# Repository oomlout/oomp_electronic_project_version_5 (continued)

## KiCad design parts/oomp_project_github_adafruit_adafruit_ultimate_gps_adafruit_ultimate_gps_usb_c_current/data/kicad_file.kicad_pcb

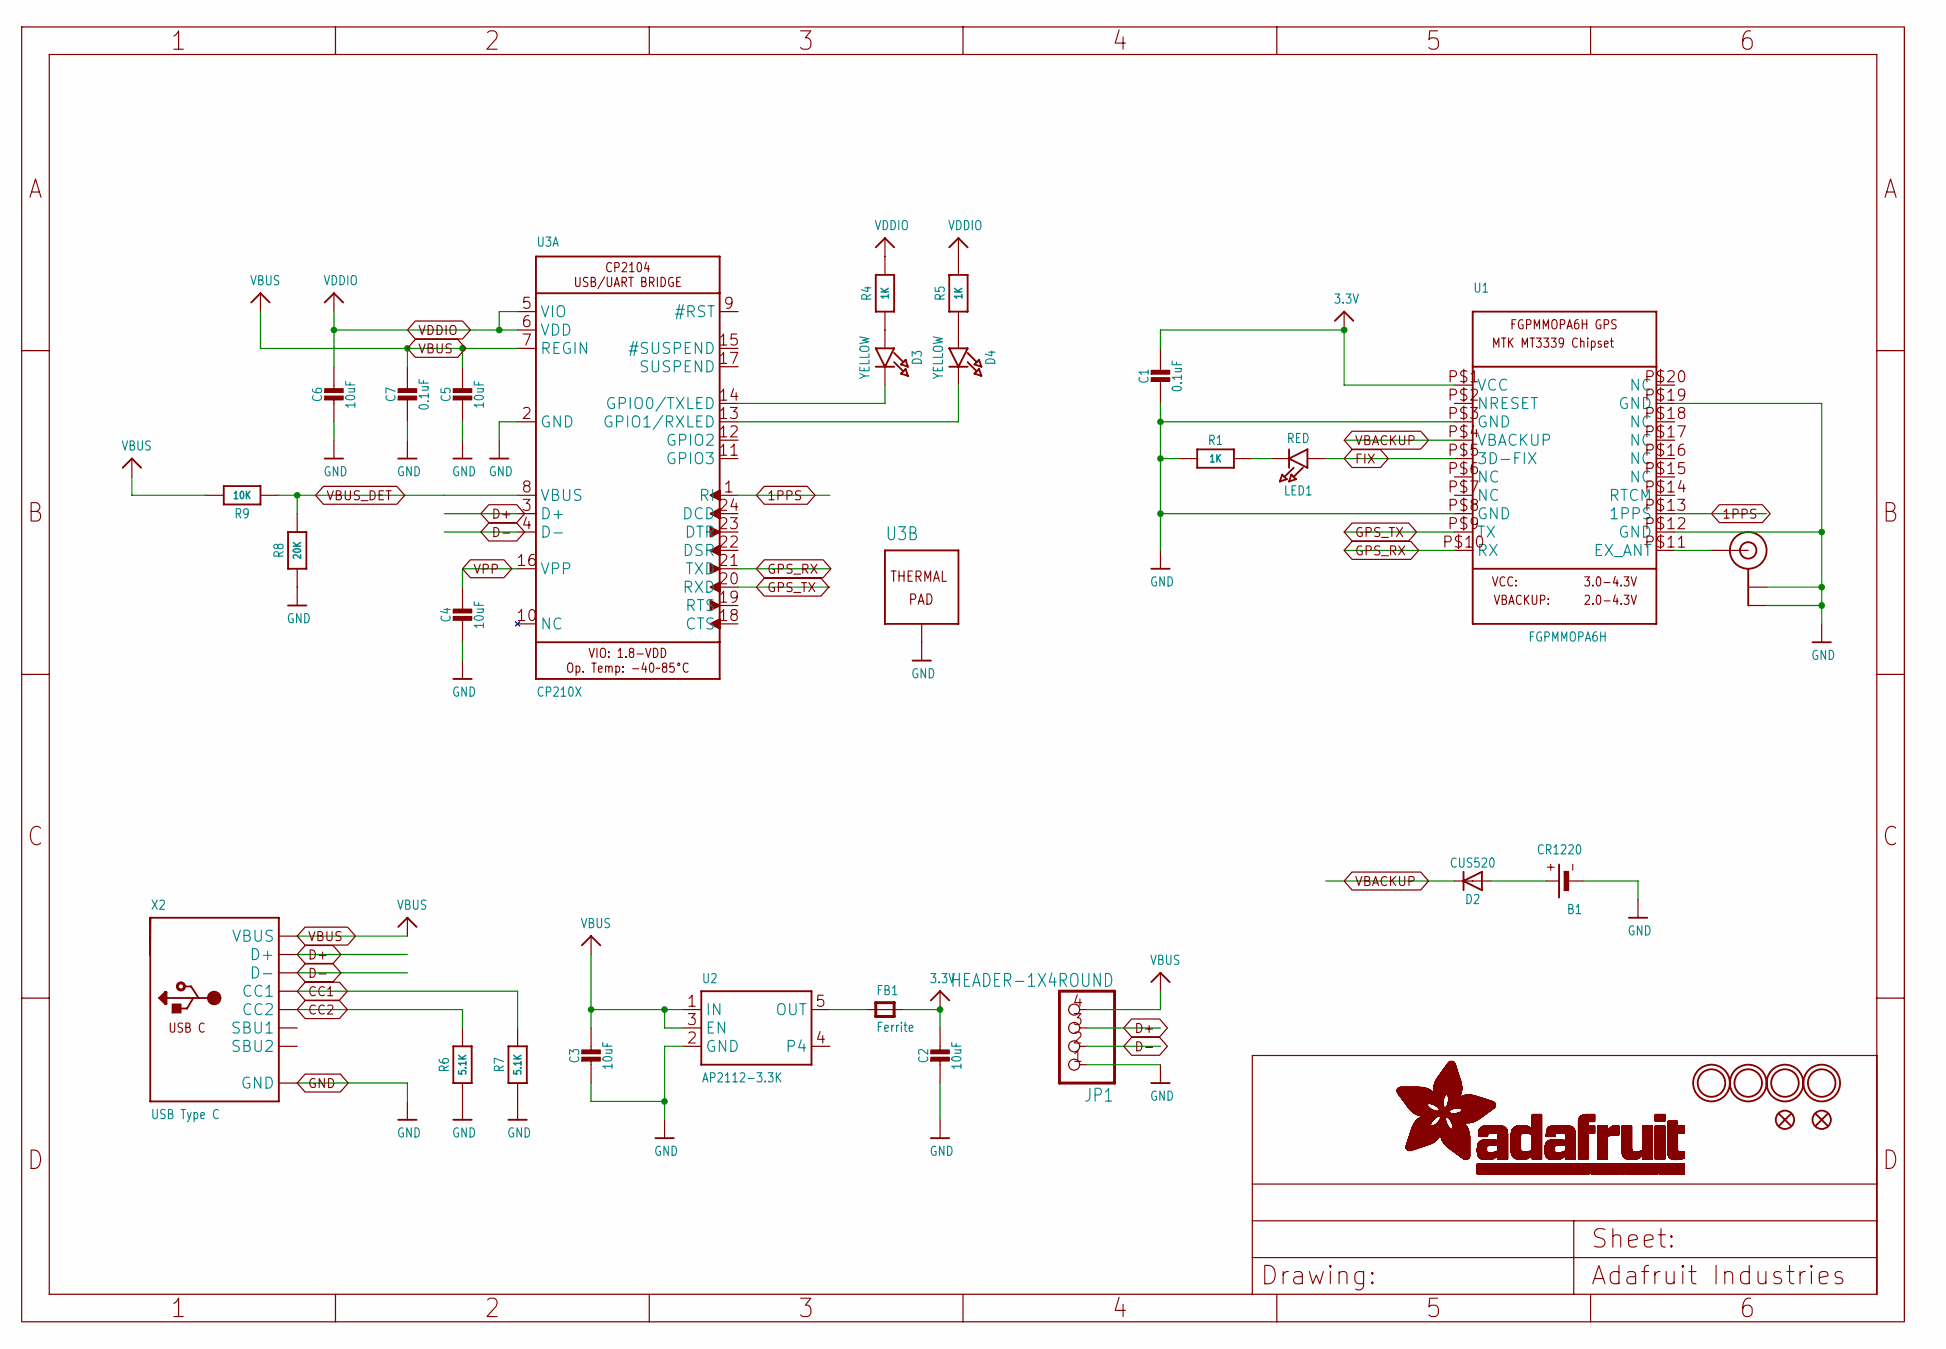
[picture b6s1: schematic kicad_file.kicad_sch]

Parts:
B1: CR1220
C1, C7: 0.1uF; 0603-NO
C2, C3, C4, C5, C6: 10uF; 0805-NO
D2: CUS520; SOD-323
D3, D4: YELLOW; CHIPLED_0805_NOOUTLINE
FB1: Ferrite; 0805-NO
FID1, FID2: FIDUCIAL_1MM
JP1: HEADER-1X4ROUND; 1X04_ROUND
LED1: RED; CHIPLED_0805_NOOUTLINE
R1, R4, R5: 1K; 0603-NO
R6, R7: 5.1K; 0603-NO
R8: 20K; 0603-NO
R9: 10K; 0603-NO
U1: FGPMMOPA6H
U2: AP2112-3.3K; SOT23-5
U3: CP210X; QFN24_4MM_SMSC
U$8, U$9, U$35, U$36: MOUNTINGHOLE2.5; MOUNTINGHOLE_2.5_PLATED
U$20: U.FL
X2: USB Type C; USB_C_CUSB31-CFM2AX-01-X

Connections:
1PPS: U1.P$13 (1PPS), U3.1 (RI)
3.3V: C1.1, C2.1, FB1.2, U1.P$1 (VCC)
CC1: R7.2, X2.A5 (CC1)
CC2: R6.2, X2.B5 (CC2)
D+: JP1.3, U3.3 (D+), X2.A6 (D+), X2.B6 (D+)
D-: JP1.2, U3.4 (D-), X2.A7 (D-), X2.B7 (D-)
FIX: LED1.A, U1.P$5 (3D-FIX)
GND: B1.-, C1.2, C2.2, C3.2, C4.2, C5.2, C6.2, C7.2, JP1.1, R1.1, R6.1, R7.1, R8.1, U1.P$3 (GND), U1.P$8 (GND), U1.P$12 (GND), U1.P$19 (GND), U2.2 (GND), U3.2 (GND), U3.THERM (TP), U$20.P$1 (GND), U$20.P$2 (GND), X2.A1B12 (GND), X2.B1A12 (GND)
GPS_RX: U1.P$10 (RX), U3.21 (TXD)
GPS_TX: U1.P$9 (TX), U3.20 (RXD)
unnamed: B1.+$1 (+), B1.+$2 (+), D2.A
unnamed: LED1.C, R1.2
unnamed: FB1.1, U2.5 (OUT)
unnamed: U1.P$11 (EX_ANT), U$20.P$3 (SIGNAL)
unnamed: D3.A, R4.1
unnamed: D4.A, R5.1
unnamed: D3.C, U3.14 (GPIO0/TXLED)
unnamed: D4.C, U3.13 (GPIO1/RXLED)
VBACKUP: D2.C, U1.P$4 (VBACKUP)
VBUS: C3.1, C5.1, C7.1, JP1.4, R9.2, U2.1 (IN), U2.3 (EN), U3.7 (REGIN), X2.A4B9 (VBUS), X2.B4A9 (VBUS)
VBUS_DET: R8.2, R9.1, U3.8 (VBUS)
VDDIO: C6.1, R4.2, R5.2, U3.5 (VIO), U3.6 (VDD)
VPP: C4.1, U3.16 (VPP)

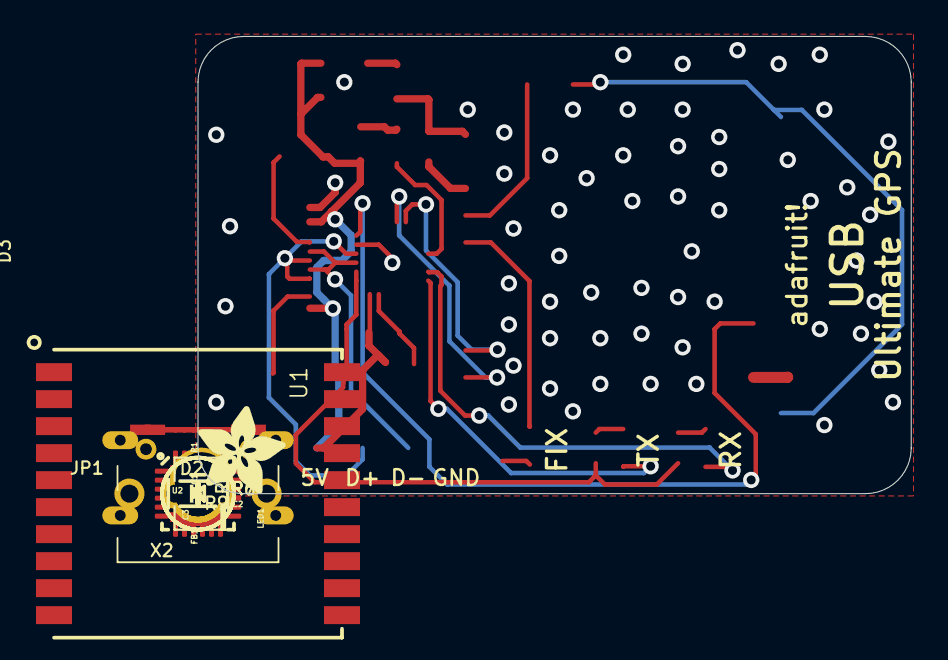
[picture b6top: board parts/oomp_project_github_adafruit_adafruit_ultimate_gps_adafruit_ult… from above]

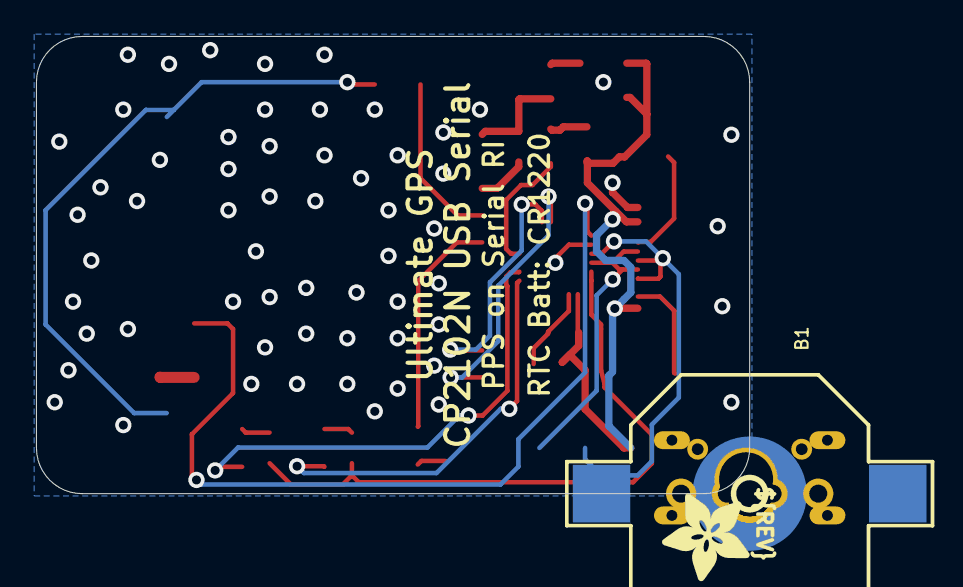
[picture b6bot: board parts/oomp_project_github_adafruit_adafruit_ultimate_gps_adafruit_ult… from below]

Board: 2 copper layers, 39.6 x 25.4 mm, 35 parts (3 on the bottom side), 23 nets.

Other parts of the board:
U$13, U$18: ADAFRUIT_5MM
U$16: PCBFEAT-REV-040

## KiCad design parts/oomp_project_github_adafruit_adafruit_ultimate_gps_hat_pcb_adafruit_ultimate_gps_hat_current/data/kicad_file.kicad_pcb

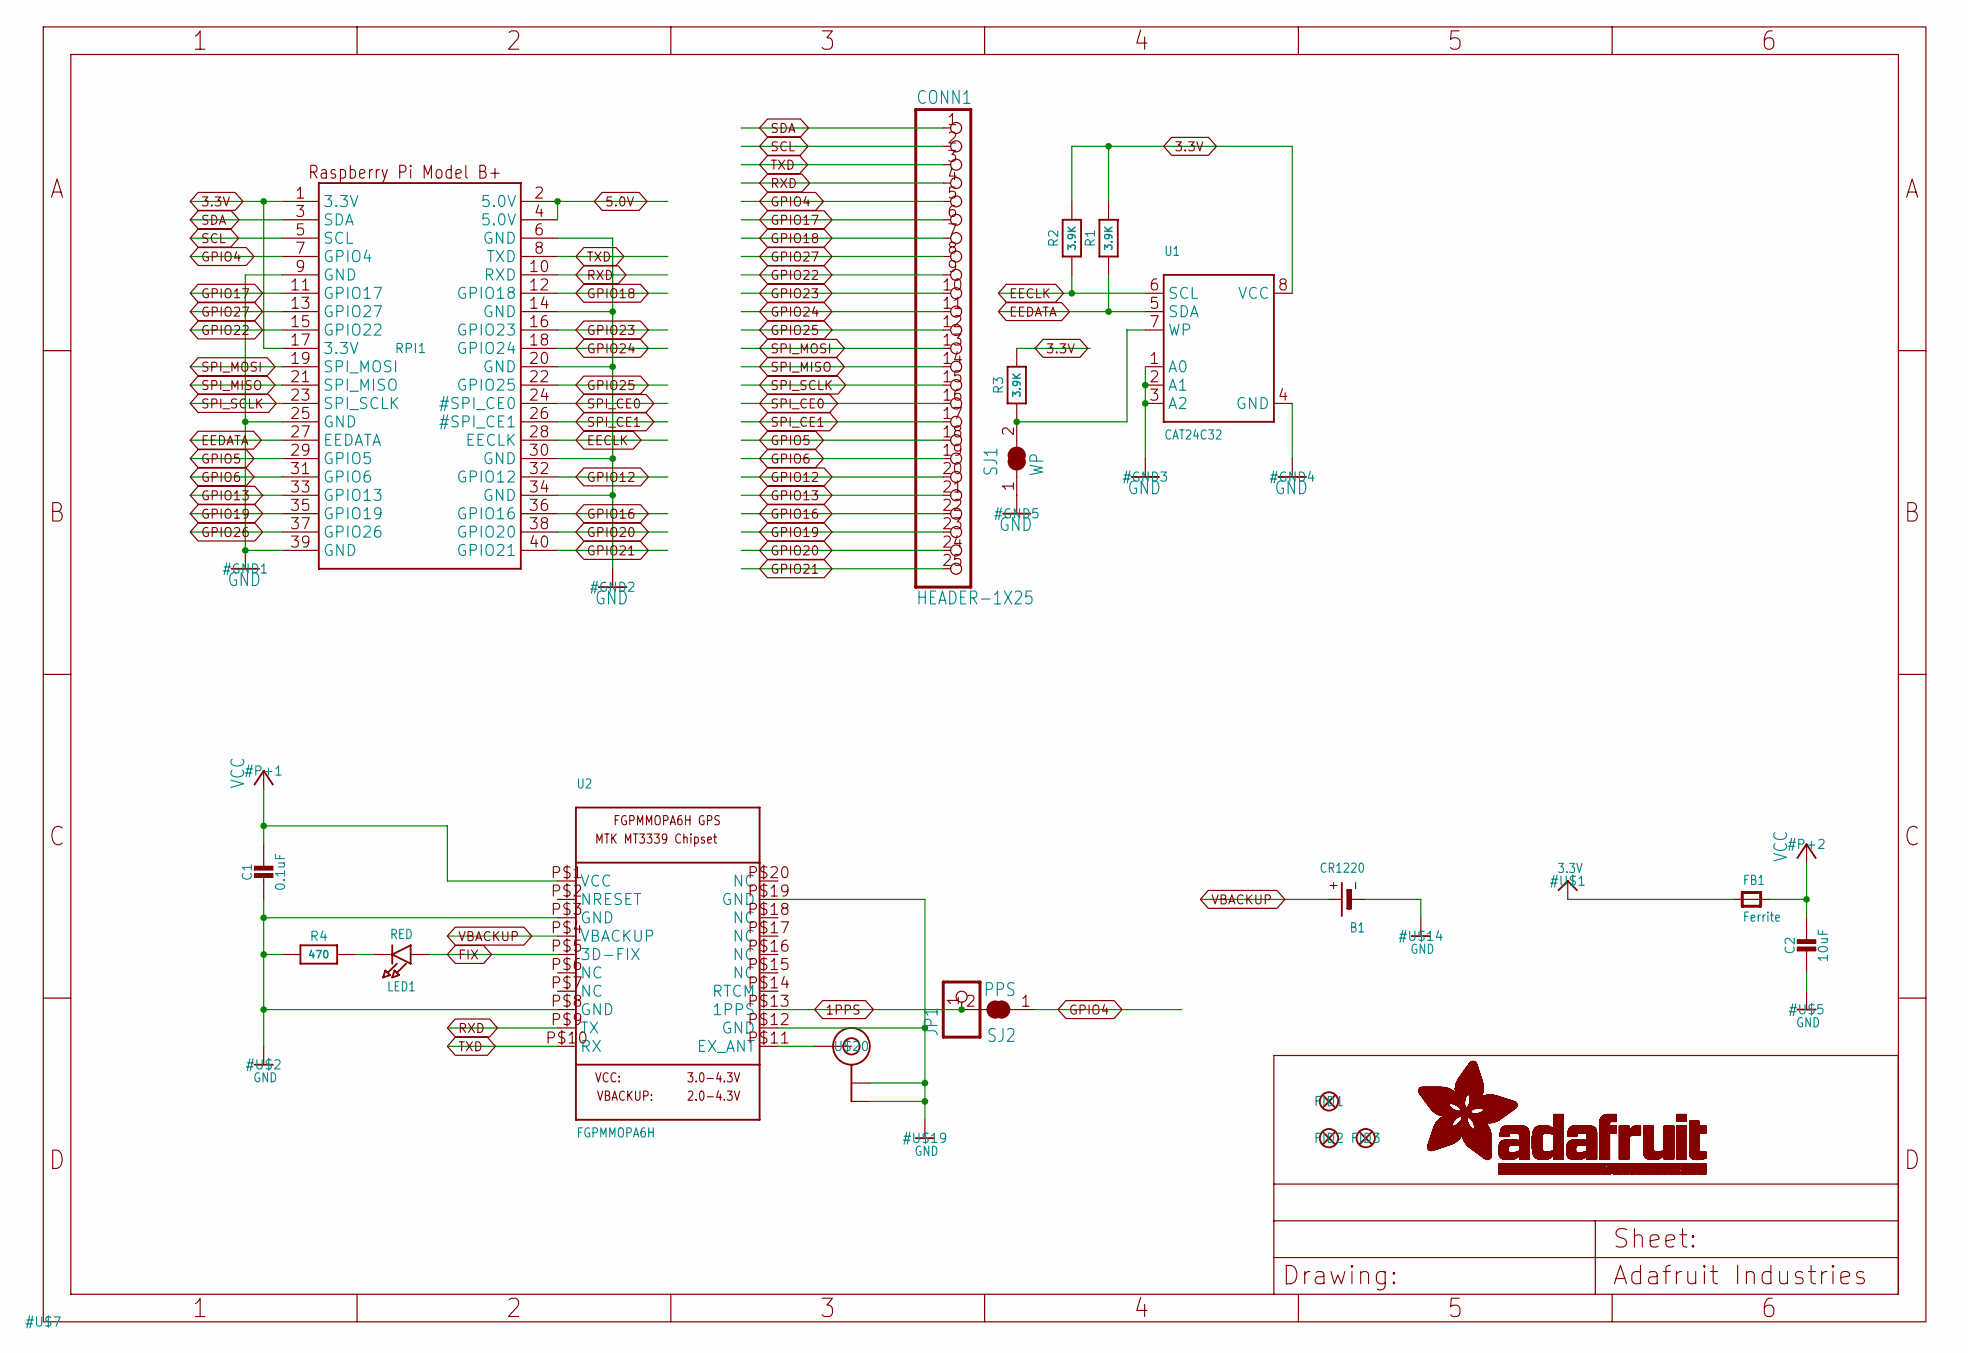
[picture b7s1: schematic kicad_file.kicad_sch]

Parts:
B1: CR1220
C1: 0.1uF; 0805-NO
C2: 10uF; 0805-NO
CONN1: HEADER-1X25; 1X25_ROUND_70MIL
FB1: Ferrite; 0805
FID1, FID2, FID3: FIDUCIAL""; FIDUCIAL_1MM
JP1: PINHD-1X1CB; 1X01-CLEANBIG
LED1: RED; CHIPLED_0805
R1, R2, R3: 3.9K; 0805-NO
R4: 470; 0805-NO
RPI1: RASPBERRYPI_BPLUS_HATSLOTS; PI_HAT_SLOTS
SJ1: WP; SOLDERJUMPER_CLOSEDWIRE
SJ2: PPS; SOLDERJUMPER_CLOSEDWIRE
U1: CAT24C32; SOIC8_150MIL
U2: FGPMMOPA6H
U$20: U.FL

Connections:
1PPS: JP1.1, SJ2.2, U2.P$13 (1PPS)
3.3V: FB1.1, R1.2, R2.2, R3.2, RPI1.1 (3.3V), RPI1.17 (3.3V), U1.8 (VCC)
5.0V: RPI1.2 (5.0V), RPI1.4 (5.0V)
EECLK: R2.1, RPI1.28 (EECLK), U1.6 (SCL)
EEDATA: R1.1, RPI1.27 (EEDATA), U1.5 (SDA)
FIX: LED1.A, U2.P$5 (3D-FIX)
GND: B1.-, C1.2, C2.2, R4.1, RPI1.6 (GND), RPI1.9 (GND), RPI1.14 (GND), RPI1.20 (GND), RPI1.25 (GND), RPI1.30 (GND), RPI1.34 (GND), RPI1.39 (GND), SJ1.1, U1.1 (A0), U1.2 (A1), U1.3 (A2), U1.4 (GND), U2.P$3 (GND), U2.P$8 (GND), U2.P$12 (GND), U2.P$19 (GND), U$20.P$1 (GND), U$20.P$2 (GND)
GPIO4: CONN1.5, RPI1.7 (GPIO4), SJ2.1
GPIO5: CONN1.18, RPI1.29 (GPIO5)
GPIO6: CONN1.19, RPI1.31 (GPIO6)
GPIO12: CONN1.20, RPI1.32 (GPIO12)
GPIO13: CONN1.21, RPI1.33 (GPIO13)
GPIO16: CONN1.22, RPI1.36 (GPIO16)
GPIO17: CONN1.6, RPI1.11 (GPIO17)
GPIO18: CONN1.7, RPI1.12 (GPIO18)
GPIO19: CONN1.23, RPI1.35 (GPIO19)
GPIO20: CONN1.24, RPI1.38 (GPIO20)
GPIO21: CONN1.25, RPI1.40 (GPIO21)
GPIO22: CONN1.9, RPI1.15 (GPIO22)
GPIO23: CONN1.10, RPI1.16 (GPIO23)
GPIO24: CONN1.11, RPI1.18 (GPIO24)
GPIO25: CONN1.12, RPI1.22 (GPIO25)
GPIO26: RPI1.37 (GPIO26)
GPIO27: CONN1.8, RPI1.13 (GPIO27)
unnamed: R3.1, SJ1.2, U1.7 (WP)
unnamed: LED1.C, R4.2
unnamed: U2.P$11 (EX_ANT), U$20.P$3 (SIGNAL)
RXD: CONN1.4, RPI1.10 (RXD), U2.P$9 (TX)
SCL: CONN1.2, RPI1.5 (SCL)
SDA: CONN1.1, RPI1.3 (SDA)
SPI_CE0: CONN1.16, RPI1.24 (#SPI_CE0)
SPI_CE1: CONN1.17, RPI1.26 (#SPI_CE1)
SPI_MISO: CONN1.14, RPI1.21 (SPI_MISO)
SPI_MOSI: CONN1.13, RPI1.19 (SPI_MOSI)
SPI_SCLK: CONN1.15, RPI1.23 (SPI_SCLK)
TXD: CONN1.3, RPI1.8 (TXD), U2.P$10 (RX)
VBACKUP: B1.+$1 (+), U2.P$4 (VBACKUP)
VCC: C1.1, C2.1, FB1.2, U2.P$1 (VCC)

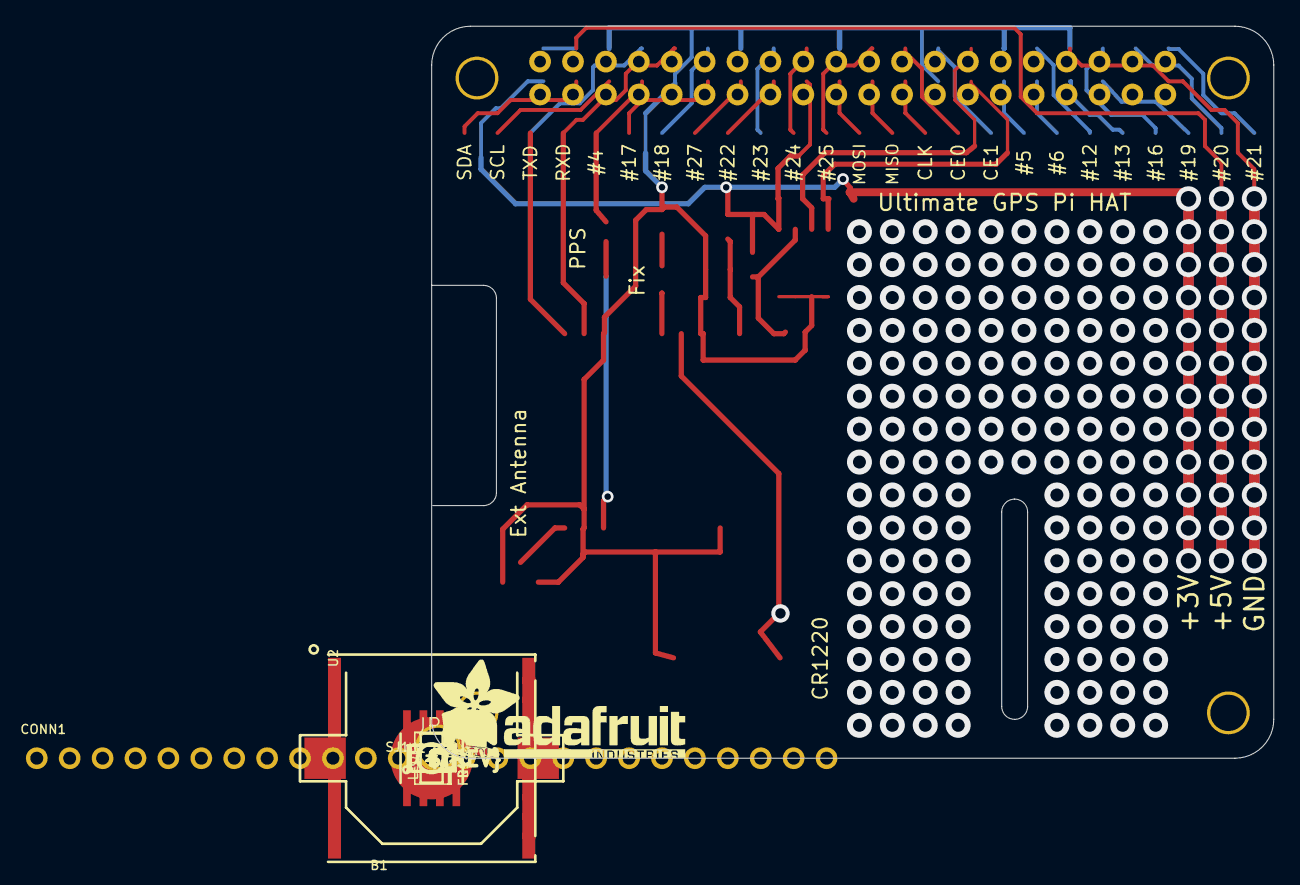
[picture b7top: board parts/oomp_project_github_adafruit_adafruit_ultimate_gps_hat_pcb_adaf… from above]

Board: 2 copper layers, 65.0 x 56.5 mm, 23 parts (0 on the bottom side), 37 nets.

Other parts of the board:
U$3: ADAFRUIT_TEXT_20MM
U$4: PIHATLOGO
U$6: PCBFEAT-REV-056
